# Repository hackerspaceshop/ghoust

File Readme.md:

Ghoust is the name of the game.

There will be a game.
It will be very good.

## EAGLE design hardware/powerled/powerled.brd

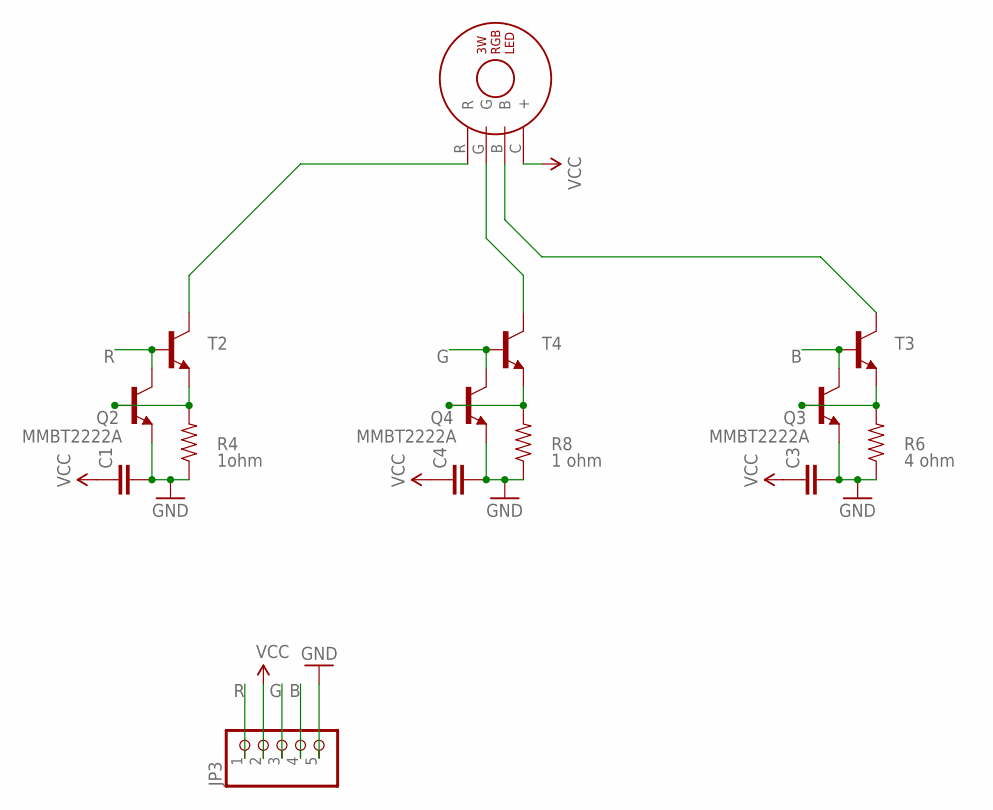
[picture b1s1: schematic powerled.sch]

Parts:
C1, C3, C4: SPARKFUN_CAP0603-CAP; SPARKFUN_0603-CAP
JP3: PINHD-1X5; 1X05
Q2, Q3, Q4: MMBT2222A; SOT23-3
R4: 1ohm; 0603-RES
R6: 4 ohm; 0603-RES
R8: 1 ohm; 0603-RES
T2, T3, T4: BCX54-NPN-SOT89-BCE; SOT89-BCE
U$1: RGB3W

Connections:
B: JP3.4, Q3.3 (C), T3.B
G: JP3.3, Q4.3 (C), T4.B
GND: C1.2, C3.2, C4.2, JP3.5, Q2.2 (E), Q3.2 (E), Q4.2 (E), R4.1, R6.1, R8.1
unnamed: T2.C, U$1.R
unnamed: T4.C, U$1.G
unnamed: T3.C, U$1.B
unnamed: Q2.1 (B), R4.2, T2.E
unnamed: Q3.1 (B), R6.2, T3.E
unnamed: Q4.1 (B), R8.2, T4.E
R: JP3.1, Q2.3 (C), T2.B
VCC: C1.1, C3.1, C4.1, JP3.2, U$1.C (+)

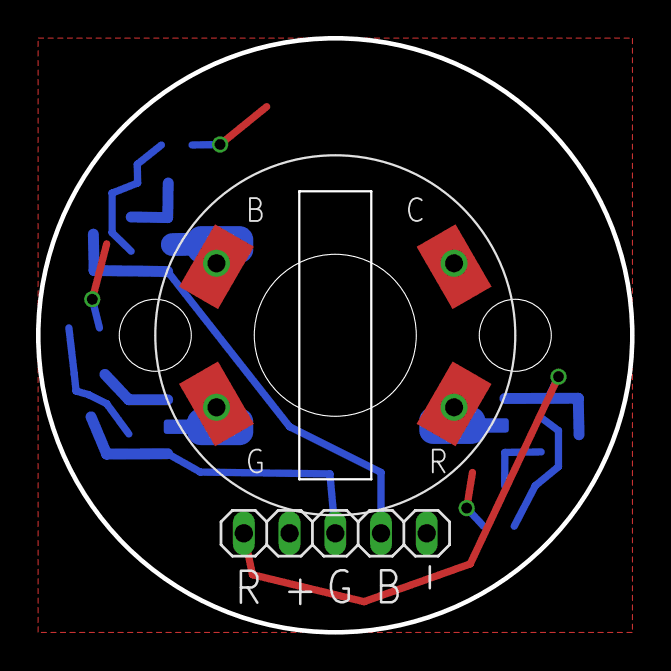
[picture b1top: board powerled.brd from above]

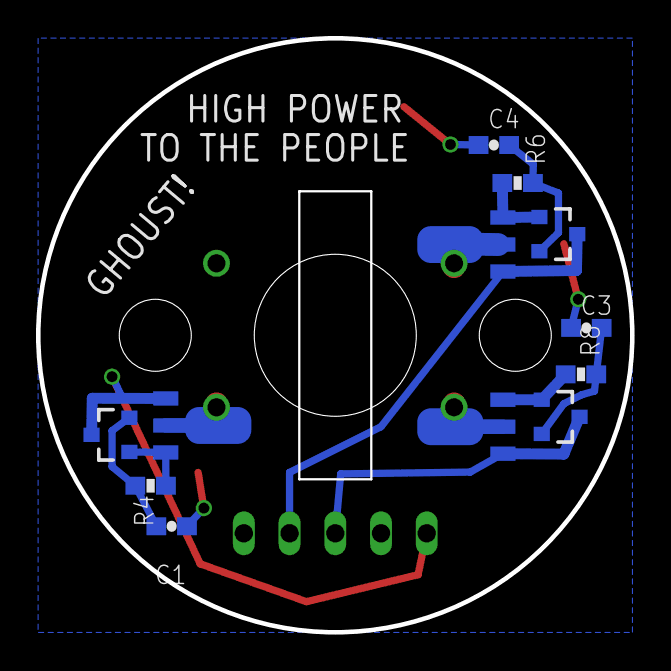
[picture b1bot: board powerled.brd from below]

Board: 2 copper layers, 33.0 x 33.0 mm, 14 parts (12 on the bottom side), 11 nets.

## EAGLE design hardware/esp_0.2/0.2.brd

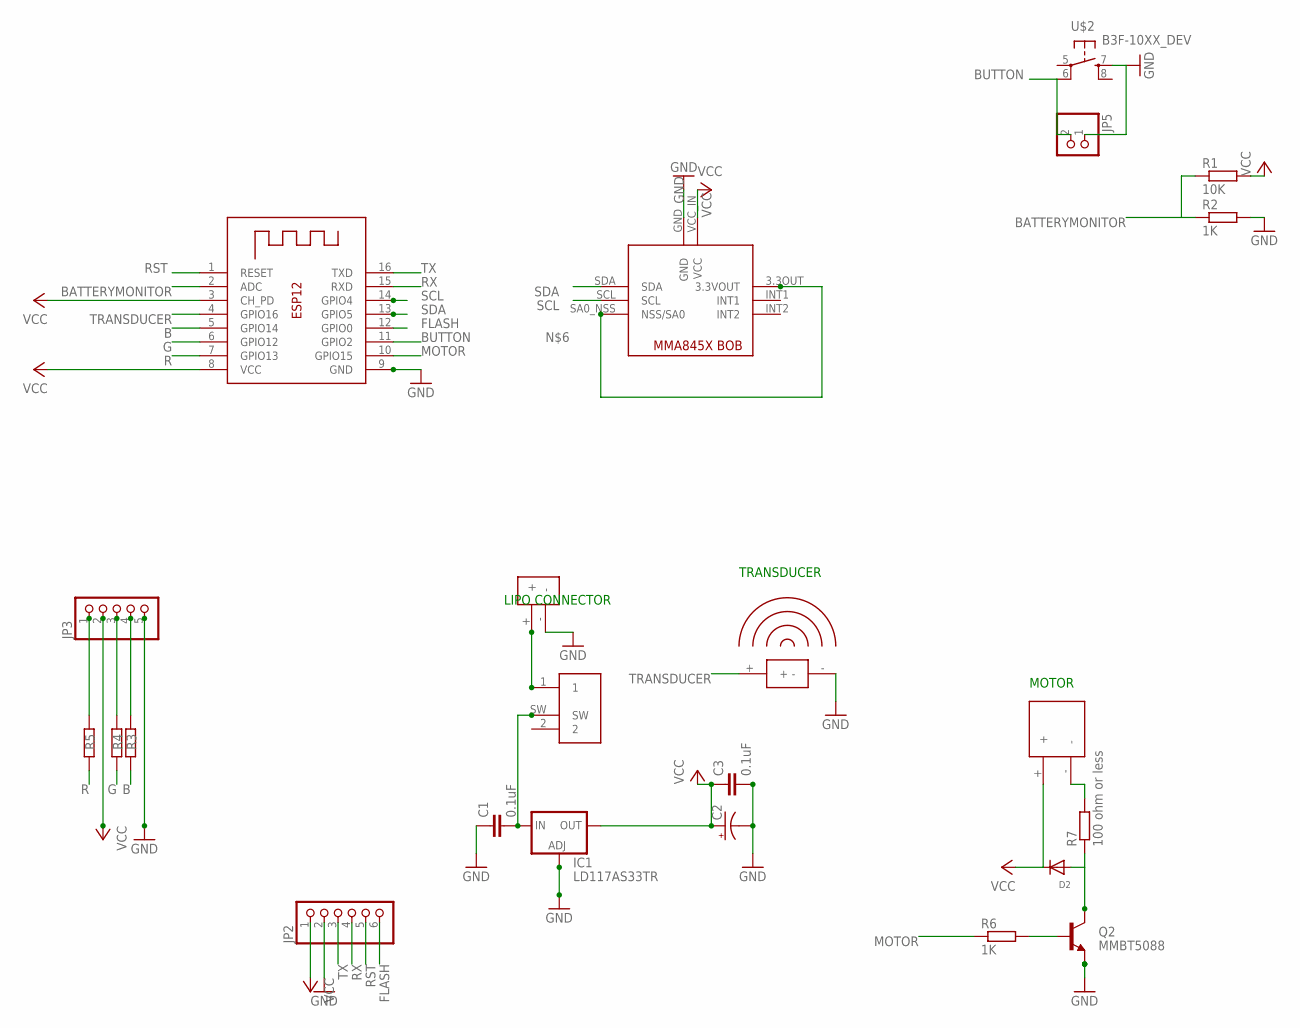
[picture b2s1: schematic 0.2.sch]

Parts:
C1, C3: 0.1uF; 0805
C2: 100UF-25V-20%(PTH); CPOL-RADIAL-100UF-25V
D2: DIODE_SOD-123FL; SOD-123FL
IC1: LD117AS33TR; SOT223
JP2: PINHD-1X6; 1X06
JP3: PINHD-1X5; 1X05
JP5: PINHD-1X2/90; 1X02/90
Q2: MMBT5088; SOT23-3
R1: 10K; R0805
R2, R3, R4, R5, R6: 1K; R0805
R7: 100 ohm or less; R0805
U$1: MMA845X_BREAKOUT; MMA845XBOB
U$2: B3F-10XX_DEV; B3F-10XX
U$8: TRANSDUCER; BMT1205XH7.5
U$11: MICROSWITCH; MICR_SCHIEBESCHALTER_CHINA_PAC
U$12: VIBROMOTOR; VIBRO
U$13: LIPO; LIPOCON
X2: ESP-12

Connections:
B: R3.1, X2.5 (GPIO14)
BATTERYMONITOR: R1.1, R2.1, X2.2 (ADC)
BUTTON: JP5.2, U$2.6 (P1), X2.11 (GPIO2)
FLASH: JP2.6, X2.12 (GPIO0)
G: R4.1, X2.6 (GPIO12)
GND: C1.1, C2.2 (-), C3.2, IC1.1 (ADJ), JP2.2, JP3.5, JP5.1, Q2.2 (E), R2.2, U$1.GND, U$2.7 (S), U$8.-, U$13.-, X2.9 (GND)
MOTOR: R6.1, X2.10 (GPIO15)
unnamed: R7.2, U$12.-
unnamed: U$11.1, U$13.+
unnamed: D2.A, Q2.3 (C), R7.1
unnamed: Q2.1 (B), R6.2
unnamed: C1.2, IC1.3 (IN), U$11.SW
unnamed: U$1.3.3OUT (3.3VOUT), U$1.SA0_NSS (NSS/SA0)
R: R5.1, X2.7 (GPIO13)
RST: JP2.5, X2.1 (RESET)
RX: JP2.4, X2.15 (RXD)
SCL: U$1.SCL, X2.14 (GPIO4)
SDA: U$1.SDA, X2.13 (GPIO5)
TRANSDUCER: U$8.+, X2.4 (GPIO16)
TX: JP2.3, X2.16 (TXD)
VCC: C2.1 (+), C3.1, D2.C, IC1.4 (OUT), JP2.1, JP3.2, R1.2, U$1.VCC_IN (VCC), U$12.+, X2.3 (CH_PD), X2.8 (VCC)
XX: JP3.1, R5.2
XXX: JP3.3, R4.2
XXXX: JP3.4, R3.2

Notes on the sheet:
MOTOR
LIPO CONNECTOR
TRANSDUCER

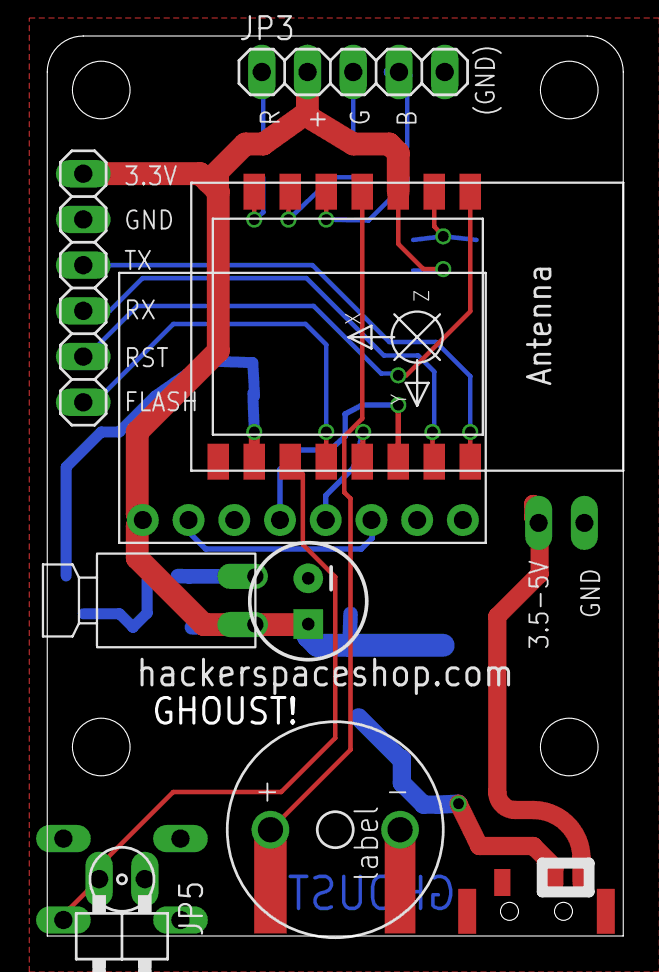
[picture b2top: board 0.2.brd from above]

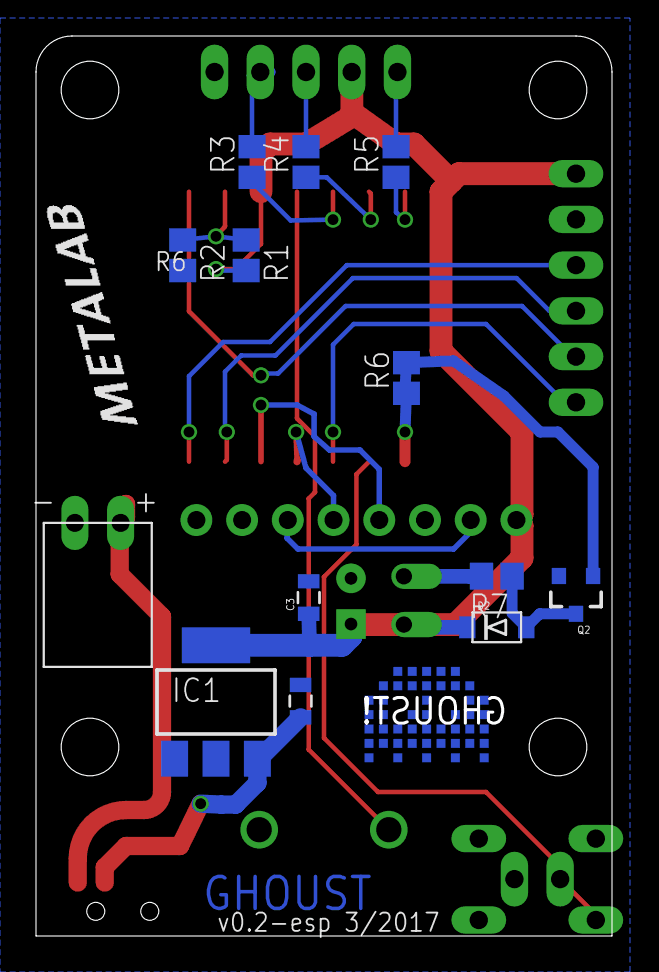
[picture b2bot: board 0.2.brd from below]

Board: 2 copper layers, 32.0 x 50.0 mm, 25 parts (15 on the bottom side), 24 nets.

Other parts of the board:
U$4: METALAB
U$6: GHOUT_LOGO; GHOUST_LOGO

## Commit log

2017-03-06 You must read this. See? You just did.
2017-03-06 First experimental revision of the arduino code
2017-03-07 initial commit of ghoust backend
2017-03-07 Eagle files .. evolving
2017-03-08 changes in debug clients, added game tree function
2017-03-08 fixed bug on disconnect of client
2017-03-08 initial draft of modular games interface, working for single game
2017-03-08 initial draft of modular games interface, working for single game (missed two files in prev. commit)
2017-03-23 modular games and choosing method working (not field tested)
2017-03-28 added wifimangaer for captive portal config
2017-03-29 progress of the recent debug session, various fixes and enhancements. contains temporary fix for led color inversion bug. ghoust_game is currently set to run with only one client connected, this make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
2017-04-16 Removed use of "String"-handling, Fixed tone() bug
2017-04-16 added timeout to led color RAW mode
2017-04-17 Added Rainbow led effect
2017-04-17 Added battery monitor + minor bugfixes / cleanup
2017-04-17 Minor fixes
2017-04-17 Accelerometer cleanup
2017-04-22 fixed led duration, removed led color hotfix, remove ghoust_game debug change
2017-04-22 python updates
2017-04-22 added ghoust_teamgame, some small fixes in player object, fixed debug clients (wrong config parameter)
2017-04-23 added game-change via mqtt (GHOUST/server/changegame)
2017-04-23 added argparse and a little errorhandling

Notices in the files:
parts and their libraries:
SparkFun-DiscreteSemi: Licensing: Creative Commons ShareAlike 4.0 International - https://creativecommons.org/licenses/by-sa/4.0
